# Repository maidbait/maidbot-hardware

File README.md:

# maidbot-hardware
hardware repo for the maidbot

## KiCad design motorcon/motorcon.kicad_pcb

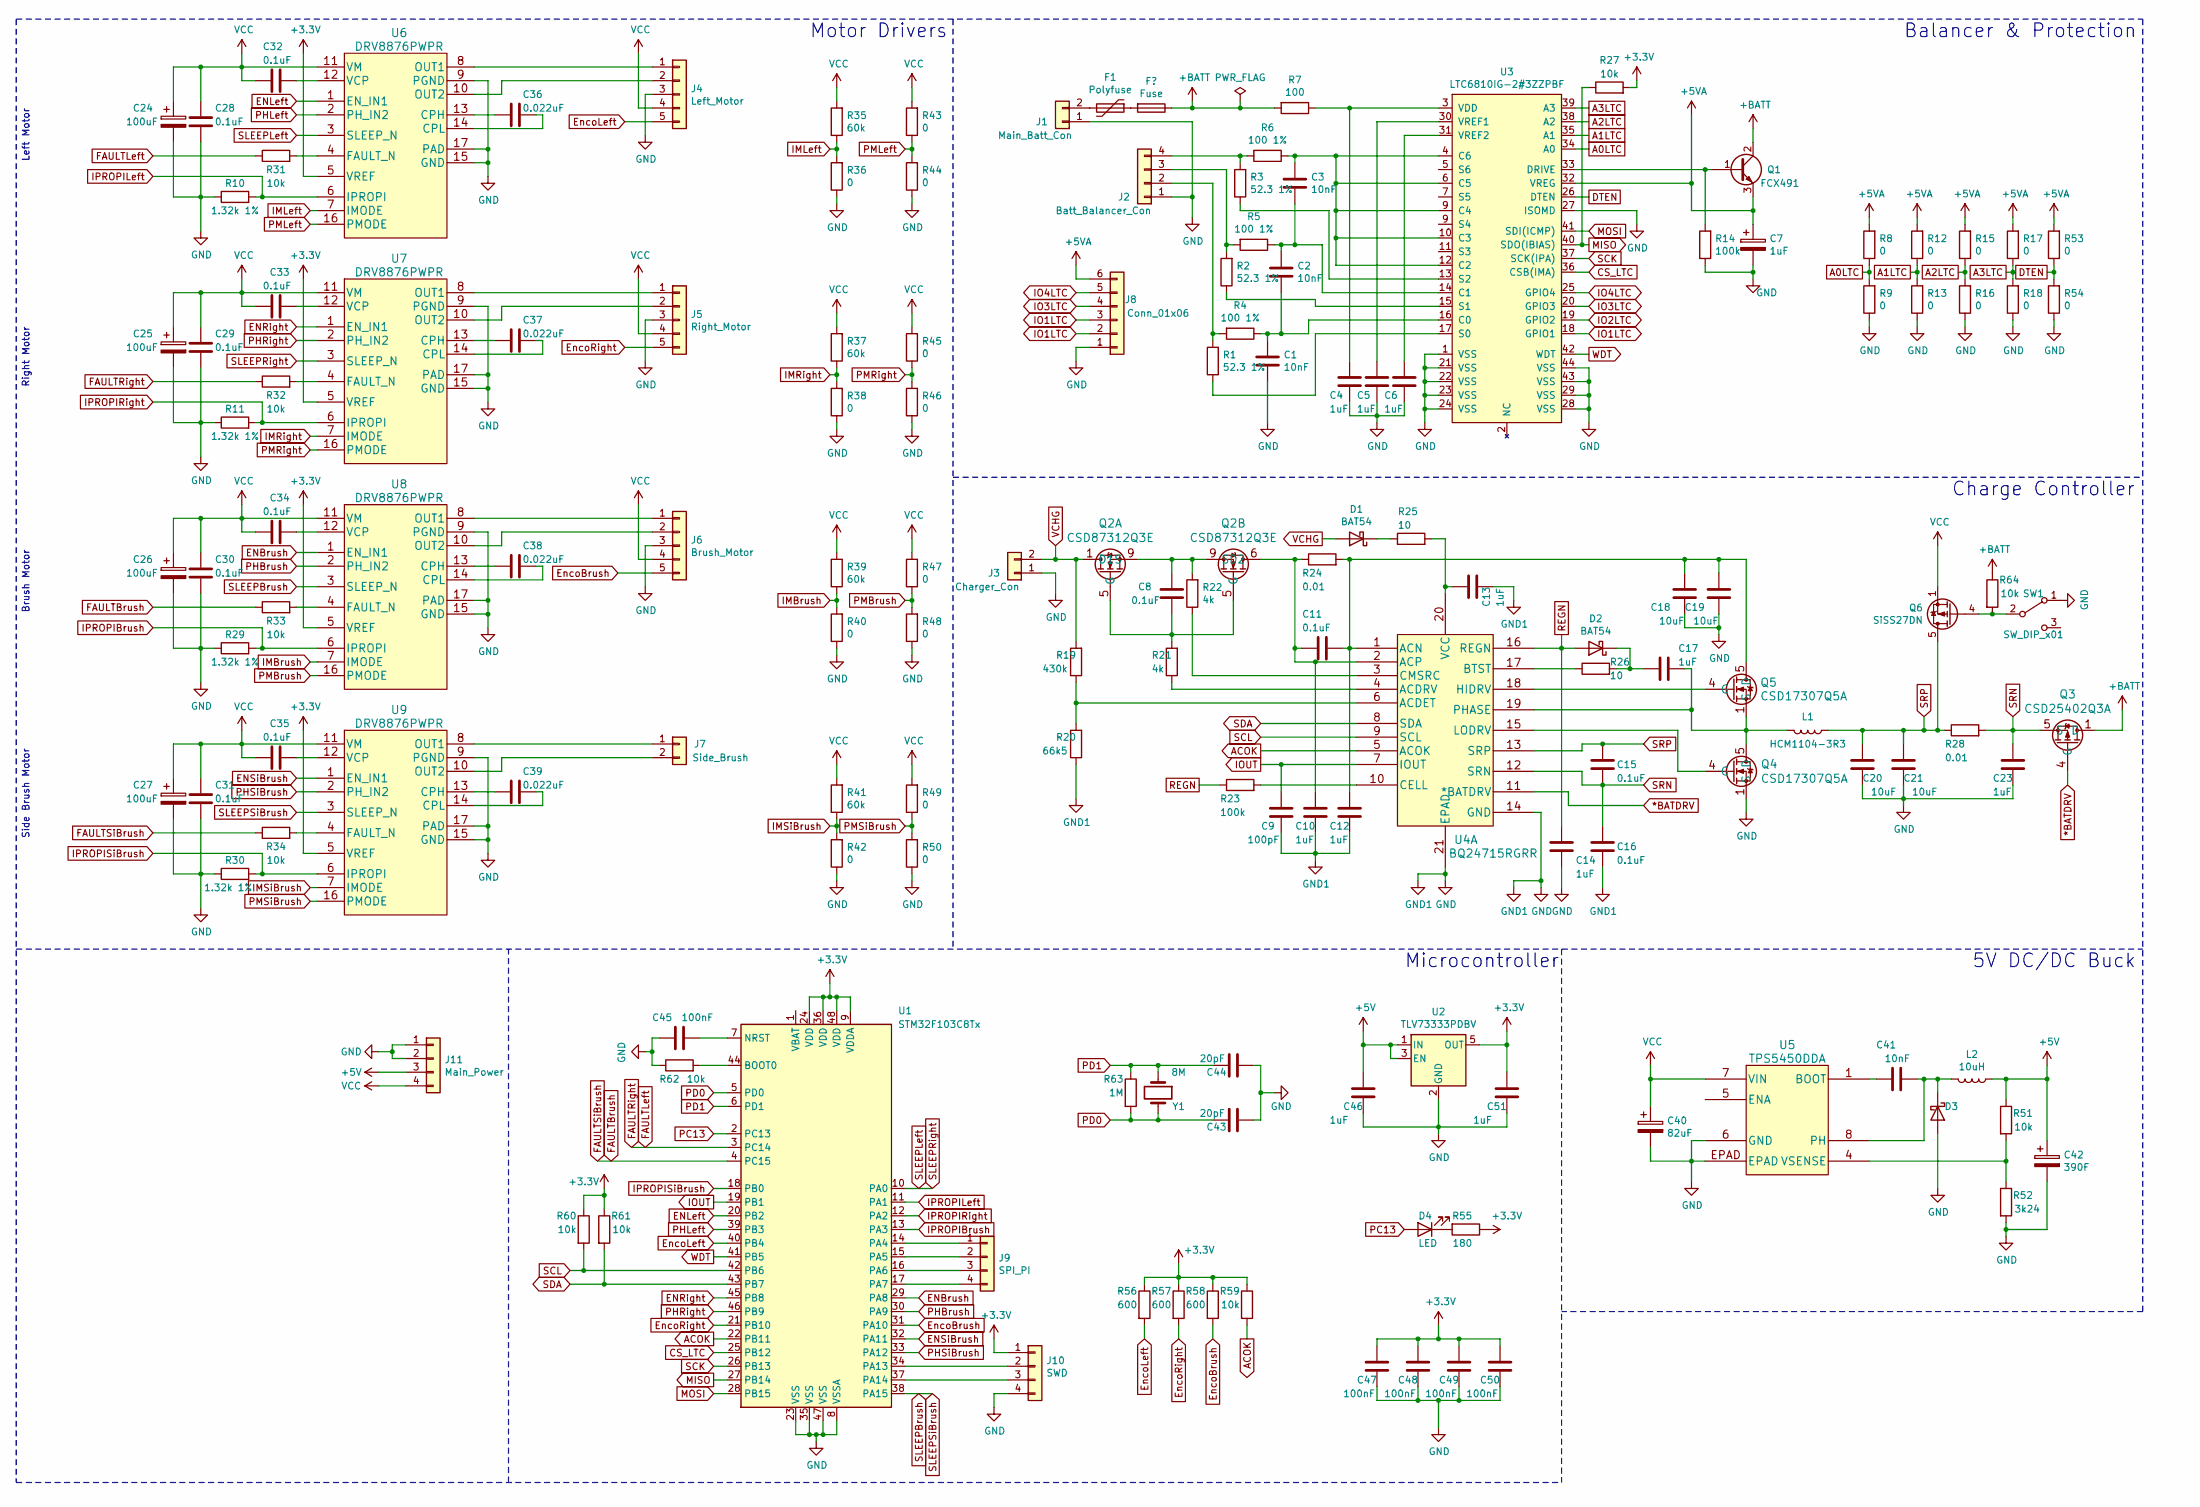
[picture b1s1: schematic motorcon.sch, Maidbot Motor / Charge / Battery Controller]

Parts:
C1, C2, C3, C41: 10nF; C_0805_2012Metric; LCSC C52278
C4, C5, C6, C10, C12, C13, C14, C17, C23, C46, C51: 1uF; C_0805_2012Metric; LCSC C282736
C7: 1uF; C_Elec_4x5.4; LCSC C3348
C8, C11, C15, C16, C28, C29, C30, C31, C32, C33, C34, C35: 0.1uF; C_0805_2012Metric; LCSC C476766
C9: 100pF; C_0805_2012Metric; LCSC C1790
C18, C19, C20, C21: 10uF; C_0805_2012Metric; LCSC C17024
C24, C25, C26, C27: 100uF; C_Radial_D6.3mm_H11.0mm_P2.50mm
C36, C37, C38, C39: 0.022uF; C_0805_2012Metric; LCSC C24658
C40: 82uF; CP_Elec_10x10; LCSC C413517
C42: 390F; CP_Elec_10x10; LCSC C359223
C43, C44: 20pF; C_0805_2012Metric; LCSC C94472
C45, C47, C48, C49, C50: 100nF; C_0805_2012Metric; LCSC C1711
D1, D2: BAT54; D_SOT-23_ANK; LCSC C369922
D3: BAT54; D_SMB; LCSC C32513
D4: LED; LED_0603_1608Metric; LCSC C84263
F1: Polyfuse; 16R1400GH
J1: Main_Batt_Con; AMASS_XT30UPB-M_1x02_P5.0mm_Vertical; LCSC C428721
J2: Batt_Balancer_Con; JST_PH_B4B-PH-K_1x04_P2.00mm_Vertical
J3: Charger_Con; JST_VH_B2P-VH_1x02_P3.96mm_Vertical; LCSC C138453
J4: Left_Motor; JST_PH_B5B-PH-K_1x05_P2.00mm_Vertical
J5: Right_Motor; JST_PH_B5B-PH-K_1x05_P2.00mm_Vertical
J6: Brush_Motor; JST_PH_B5B-PH-K_1x05_P2.00mm_Vertical
J7: Side_Brush; JST_PH_B2B-PH-K_1x02_P2.00mm_Vertical
J8: Conn_01x06; JST_PH_B5B-PH-K_1x05_P2.00mm_Vertical
J9: SPI_PI; JST_PH_B5B-PH-K_1x05_P2.00mm_Vertical
J10: SWD; JST_PH_S4B-PH-K_1x04_P2.00mm_Horizontal
J11: Main_Power; Molex_Mini-Fit_Jr_5569-04A2_2x02_P4.20mm_Horizontal; LCSC C234187
L1: HCM1104-3R3; LCSC C427317
L2: 10uH; BCIHP1770HC; LCSC C237980
Q1: FCX491; SOT-89-3; LCSC C156315
Q2: CSD87312Q3E; LCSC C553144
Q3: CSD25402Q3A; LCSC C111356
Q4, Q5: CSD17307Q5A; LCSC C139362
Q6: SiSS27DN; Vishay_PowerPAK_1212-8_Single
R1, R2, R3: 52.3 1%; R_0805_2012Metric; LCSC C334920
R4, R5, R6: 100 1%; R_0805_2012Metric; LCSC C103902
R7: 100; R_0805_2012Metric; LCSC C103909
R8, R9, R12, R13, R15, R16, R17, R18, R36, R38, R40, R42, R43, R44, R45, R46, R47, R48, R49, R50, R53, R54: 0; R_0805_2012Metric; LCSC C17477
R10, R11, R29, R30: 1.32k 1%; R_0805_2012Metric
R14, R23: 100k; R_0805_2012Metric; LCSC C149504
R19: 430k; R_0805_2012Metric; LCSC C17692
R20: 66k5; R_0805_2012Metric; LCSC C17791
R21, R22: 4k; R_0805_2012Metric; LCSC C17663
R24, R28: 0.01; R_1206_3216Metric; LCSC C309628
R25, R26: 10; R_0805_2012Metric; LCSC C17415
R27, R31, R32, R33, R34, R51, R59, R60, R61, R62, R64: 10k; R_0805_2012Metric; LCSC C17414
R35, R37, R39, R41: 60k; R_0805_2012Metric; LCSC C170940
R52: 3k24; R_0805_2012Metric; LCSC C17609
R55: 180; R_0805_2012Metric; LCSC C104048
R56, R57, R58: 600; R_0805_2012Metric; LCSC C17777
R63: 1M; R_0805_2012Metric; LCSC C17777
SW1: SW_DIP_x01; SS-12D28L4
U1: STM32F103C8Tx; LQFP-48_7x7mm_P0.5mm; LCSC C8734
U2: TLV73333PDBV; SOT-23-5; LCSC C134139
U3: LTC6810IG-2#3ZZPBF; SSOP-44
U4: BQ24715RGRR; LCSC C276341
U5: TPS5450DDA; LCSC C114425
U6, U7, U8, U9: DRV8876PWPR
Y1: 8M; Crystal_SMD_3225-4Pin_3.2x2.5mm; LCSC C400090

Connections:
*BATDRV: Q3.4 (G), U4.11 (*BATDRV)
+3V3: C47.1, C48.1, C49.1, C50.1, C51.1, J10.1, R27.2, R55.1, R56.1, R57.1, R58.1, R59.1, R60.1, R61.1, U1.9 (VDDA), U1.24 (VDD), U1.36 (VDD), U1.48 (VDD), U2.5 (OUT), U6.5 (VREF), U7.5 (VREF), U8.5 (VREF), U9.5 (VREF)
+5V: C42.1, C46.1, J11.3, L2.1, R51.1, U2.1 (IN), U2.3 (EN)
+5VA: C7.1, J8.6, Q1.3 (E), R8.2, R12.2, R15.2, R17.2, R53.2, U3.32 (VREG)
+BATT: F1.1, Q1.2 (C), Q3.1 (D), Q3.2 (D), Q3.3 (D), R7.2, R64.1
A0LTC: R8.1, R9.2, U3.34 (A0)
A1LTC: R12.1, R13.2, U3.35 (A1)
A2LTC: R15.1, R16.2, U3.38 (A2)
A3LTC: R17.1, R18.2, U3.39 (A3)
ACOK: R59.2, U1.22 (PB11), U4.5 (ACOK)
CS_LTC: U1.25 (PB12), U3.36 (CSB(IMA))
DTEN: R53.1, R54.2, U3.26 (DTEN)
ENBrush: U1.29 (PA8), U8.1 (EN_IN1)
ENLeft: U1.20 (PB2), U6.1 (EN_IN1)
ENRight: U1.45 (PB8), U7.1 (EN_IN1)
ENSiBrush: U1.32 (PA11), U9.1 (EN_IN1)
EncoBrush: J6.5, R58.2, U1.31 (PA10)
EncoLeft: J4.5, R56.2, U1.40 (PB4)
EncoRight: J5.5, R57.2, U1.21 (PB10)
FAULTBrush: R33.1, R34.1, U1.4 (PC15)
FAULTLeft: R31.1, R32.1, U1.3 (PC14)
GND: C1.2, C4.2, C5.2, C6.2, C7.2, C9.2, C10.2, C12.2, C13.2, C14.2, C16.2, C18.1, C19.1, C20.1, C21.1, C23.2, C24.2, C25.2, C26.2, C27.2, C28.2, C29.2, C30.2, C31.2, C40.2, C42.2, C43.1, C44.1, C45.1, C46.2, C47.2, C48.2, C49.2, C50.2, C51.2, D3.2 (A), J1.1, J2.1, J3.1, J4.3, J5.3, J6.3, J8.1, J10.4, J11.1, J11.2, Q4.1 (S), Q4.2 (S), Q4.3 (S), R9.1, R10.1, R11.1, R13.1, R14.1, R16.1, R18.1, R20.1, R29.1, R30.1, R36.1, R38.1, R40.1, R42.1, R44.1, R46.1, R48.1, R50.1, R52.2, R54.1, R62.1, SW1.1 (A), U1.8 (VSSA), U1.23 (VSS), U1.35 (VSS), U1.47 (VSS), U2.2 (GND), U3.1 (VSS), U3.21 (VSS), U3.22 (VSS), U3.23 (VSS), U3.24 (VSS), U3.27 (ISOMD), U3.28 (VSS), U3.29 (VSS), U3.43 (VSS), U3.44 (VSS), U4.14 (GND), U4.21 (EPAD), U5.6 (GND), U5.EPAD, U6.9 (PGND), U6.15 (GND), U6.17 (PAD), U7.9 (PGND), U7.15 (GND), U7.17 (PAD), U8.9 (PGND), U8.15 (GND), U8.17 (PAD), U9.9 (PGND), U9.15 (GND), U9.17 (PAD)
IMBrush: R39.1, R40.2, U8.7 (IMODE)
IMLeft: R35.1, R36.2, U6.7 (IMODE)
IMRight: R37.1, R38.2, U7.7 (IMODE)
IMSiBrush: R41.1, R42.2, U9.7 (IMODE)
IO1LTC: J8.2, J8.3, U3.18 (GPIO1)
IO2LTC: U3.19 (GPIO2)
IO3LTC: J8.4, U3.20 (GPIO3)
IO4LTC: J8.5, U3.25 (GPIO4)
IOUT: C9.1, U1.19 (PB1), U4.7 (IOUT)
IPROPIBrush: R29.2, U1.13 (PA3), U8.6 (IPROPI)
IPROPILeft: R10.2, U1.11 (PA1), U6.6 (IPROPI)
IPROPIRight: R11.2, U1.12 (PA2), U7.6 (IPROPI)
IPROPISiBrush: R30.2, U1.18 (PB0), U9.6 (IPROPI)
MISO: R27.1, U1.27 (PB14), U3.40 (SDO(IBIAS))
MOSI: U1.28 (PB15), U3.41 (SDI(ICMP))
unnamed: C1.1, C2.2, R4.1, U3.16 (C0)
unnamed: C2.1, C3.2, R5.1, U3.14 (C1)
unnamed: C3.1, R6.1, U3.4 (C6), U3.6 (C5), U3.9 (C4), U3.10 (C3), U3.12 (C2)
unnamed: C4.1, R7.1, U3.3 (VDD)
unnamed: C5.1, U3.30 (VREF1)
unnamed: C6.1, U3.31 (VREF2)
unnamed: C8.1, Q2.9 (S), R22.2
unnamed: C8.2, Q2.5 (G), R21.2
unnamed: C10.1, C11.2, Q2.6 (D2), Q2.7 (D2), Q2.8 (D2), R24.1, U4.2 (ACP)
unnamed: C11.1, C12.1, C18.2, C19.2, Q5.5 (D), Q5.6 (D), Q5.7 (D), Q5.8 (D), R24.2, U4.1 (ACN)
unnamed: C13.1, R25.2, U4.20 (VCC)
unnamed: C17.1, L1.2, Q4.5 (D), Q4.6 (D), Q4.7 (D), Q4.8 (D), Q5.1 (S), Q5.2 (S), Q5.3 (S), U4.19 (PHASE)
unnamed: C17.2, D2.1 (K), R26.2
unnamed: C32.1, U6.12 (VCP)
unnamed: C33.1, U7.12 (VCP)
unnamed: C34.1, U8.12 (VCP)
unnamed: C35.1, U9.12 (VCP)
unnamed: C36.1, U6.14 (CPL)
unnamed: C36.2, U6.13 (CPH)
unnamed: C37.1, U7.14 (CPL)
unnamed: C37.2, U7.13 (CPH)
unnamed: C38.1, U8.14 (CPL)
unnamed: C38.2, U8.13 (CPH)
unnamed: C39.1, U9.14 (CPL)
unnamed: C39.2, U9.13 (CPH)
unnamed: C41.1, U5.1 (BOOT)
unnamed: C41.2, D3.1 (K), L2.2, U5.8 (PH)
unnamed: C45.2, U1.7 (NRST)
unnamed: D1.1 (K), R25.1
unnamed: D4.1 (K), R55.2
unnamed: F1.2, J1.2
unnamed: J2.2, R1.2, R4.2
unnamed: J2.3, R2.2, R5.2
unnamed: J2.4, R3.2, R6.2
unnamed: J4.1, U6.8 (OUT1)
unnamed: J4.2, U6.10 (OUT2)
unnamed: J5.1, U7.8 (OUT1)
unnamed: J5.2, U7.10 (OUT2)
unnamed: J6.1, U8.8 (OUT1)
unnamed: J6.2, U8.10 (OUT2)
unnamed: J7.1, U9.8 (OUT1)
unnamed: J7.2, U9.10 (OUT2)
unnamed: J9.1, U1.14 (PA4)
unnamed: J9.2, U1.15 (PA5)
unnamed: J9.3, U1.16 (PA6)
unnamed: J9.4, U1.17 (PA7)
unnamed: J10.2, U1.34 (PA13)
unnamed: J10.3, U1.37 (PA14)
unnamed: Q1.1 (B), R14.2, U3.33 (DRIVE)
unnamed: Q4.4 (G), U4.15 (LODRV)
unnamed: Q5.4 (G), U4.18 (HIDRV)
unnamed: Q6.4 (G), R64.2, SW1.2 (B)
unnamed: R1.1, U3.17 (S0)
unnamed: R2.1, U3.15 (S1)
unnamed: R3.1, U3.13 (S2)
unnamed: R19.1, R20.2, U4.6 (ACDET)
unnamed: R21.1, U4.4 (ACDRV)
unnamed: R22.1, U4.3 (CMSRC)
unnamed: R23.2, U4.10 (CELL)
unnamed: R26.1, U4.17 (BTST)
unnamed: R31.2, U6.4 (FAULT_N)
unnamed: R32.2, U7.4 (FAULT_N)
unnamed: R33.2, U8.4 (FAULT_N)
unnamed: R34.2, U9.4 (FAULT_N)
unnamed: R51.2, R52.1, U5.4 (VSENSE)
unnamed: R62.2, U1.44 (BOOT0)
PC13: D4.2 (A), U1.2 (PC13)
PD0: C43.2, R63.2, U1.5 (PD0), Y1.2
PD1: C44.2, R63.1, U1.6 (PD1), Y1.1
PHBrush: U1.30 (PA9), U8.2 (PH_IN2)
PHLeft: U1.39 (PB3), U6.2 (PH_IN2)
PHRight: U1.46 (PB9), U7.2 (PH_IN2)
PHSiBrush: U1.33 (PA12), U9.2 (PH_IN2)
PMBrush: R47.1, R48.2, U8.16 (PMODE)
PMLeft: R43.1, R44.2, U6.16 (PMODE)
PMRight: R45.1, R46.2, U7.16 (PMODE)
PMSiBrush: R49.1, R50.2, U9.16 (PMODE)
REGN: C14.1, D2.2 (A), R23.1, U4.16 (REGN)
SCK: U1.26 (PB13), U3.37 (SCK(IPA))
SCL: R60.2, U1.42 (PB6), U4.9 (SCL)
SDA: R61.2, U1.43 (PB7), U4.8 (SDA)
SLEEPBrush: U1.38 (PA15), U8.3 (SLEEP_N), U9.3 (SLEEP_N)
SLEEPLeft: U1.10 (PA0), U6.3 (SLEEP_N), U7.3 (SLEEP_N)
SRN: C15.2, C16.1, C23.1, Q3.5 (S), Q3.6 (S), Q3.7 (S), Q3.8 (S), Q3.9 (S), R28.2, U4.12 (SRN)
SRP: C15.1, C20.2, C21.2, L1.1, Q6.5 (D), R28.1, U4.13 (SRP)
VCC: C24.1, C25.1, C26.1, C27.1, C28.1, C29.1, C30.1, C31.1, C32.2, C33.2, C34.2, C35.2, C40.1, J4.4, J5.4, J6.4, J11.4, Q6.1 (S), Q6.2 (S), Q6.3 (S), R35.2, R37.2, R39.2, R41.2, R43.2, R45.2, R47.2, R49.2, U5.7 (VIN), U6.11 (VM), U7.11 (VM), U8.11 (VM), U9.11 (VM)
VCHG: D1.2 (A), J3.2, Q2.1 (D1), Q2.2 (D1), Q2.3 (D1), Q2.4 (D1), R19.2
WDT: U1.41 (PB5), U3.42 (WDT)

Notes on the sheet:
Balancer & Protection
Charge Controller
5V DC/DC Buck
Motor Drivers
Left Motor
Right Motor
Brush Motor
Side Brush Motor
Microcontroller

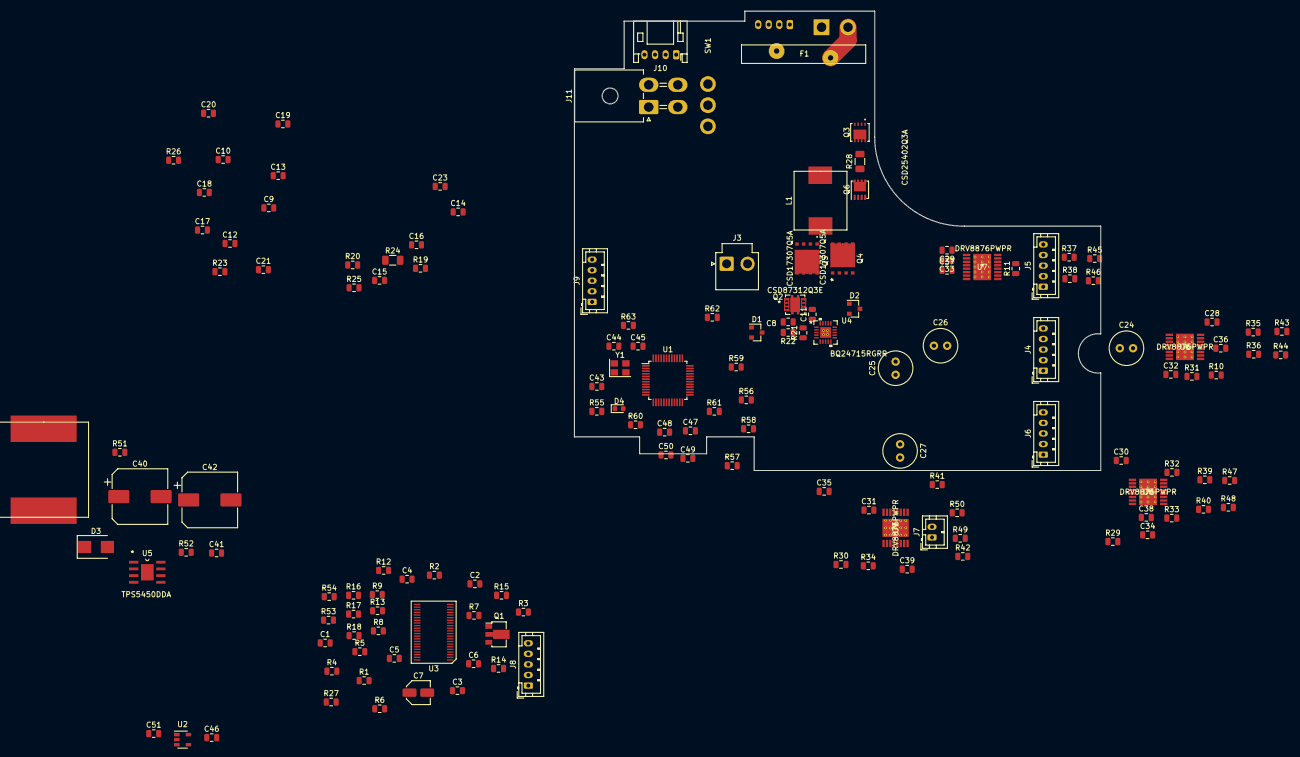
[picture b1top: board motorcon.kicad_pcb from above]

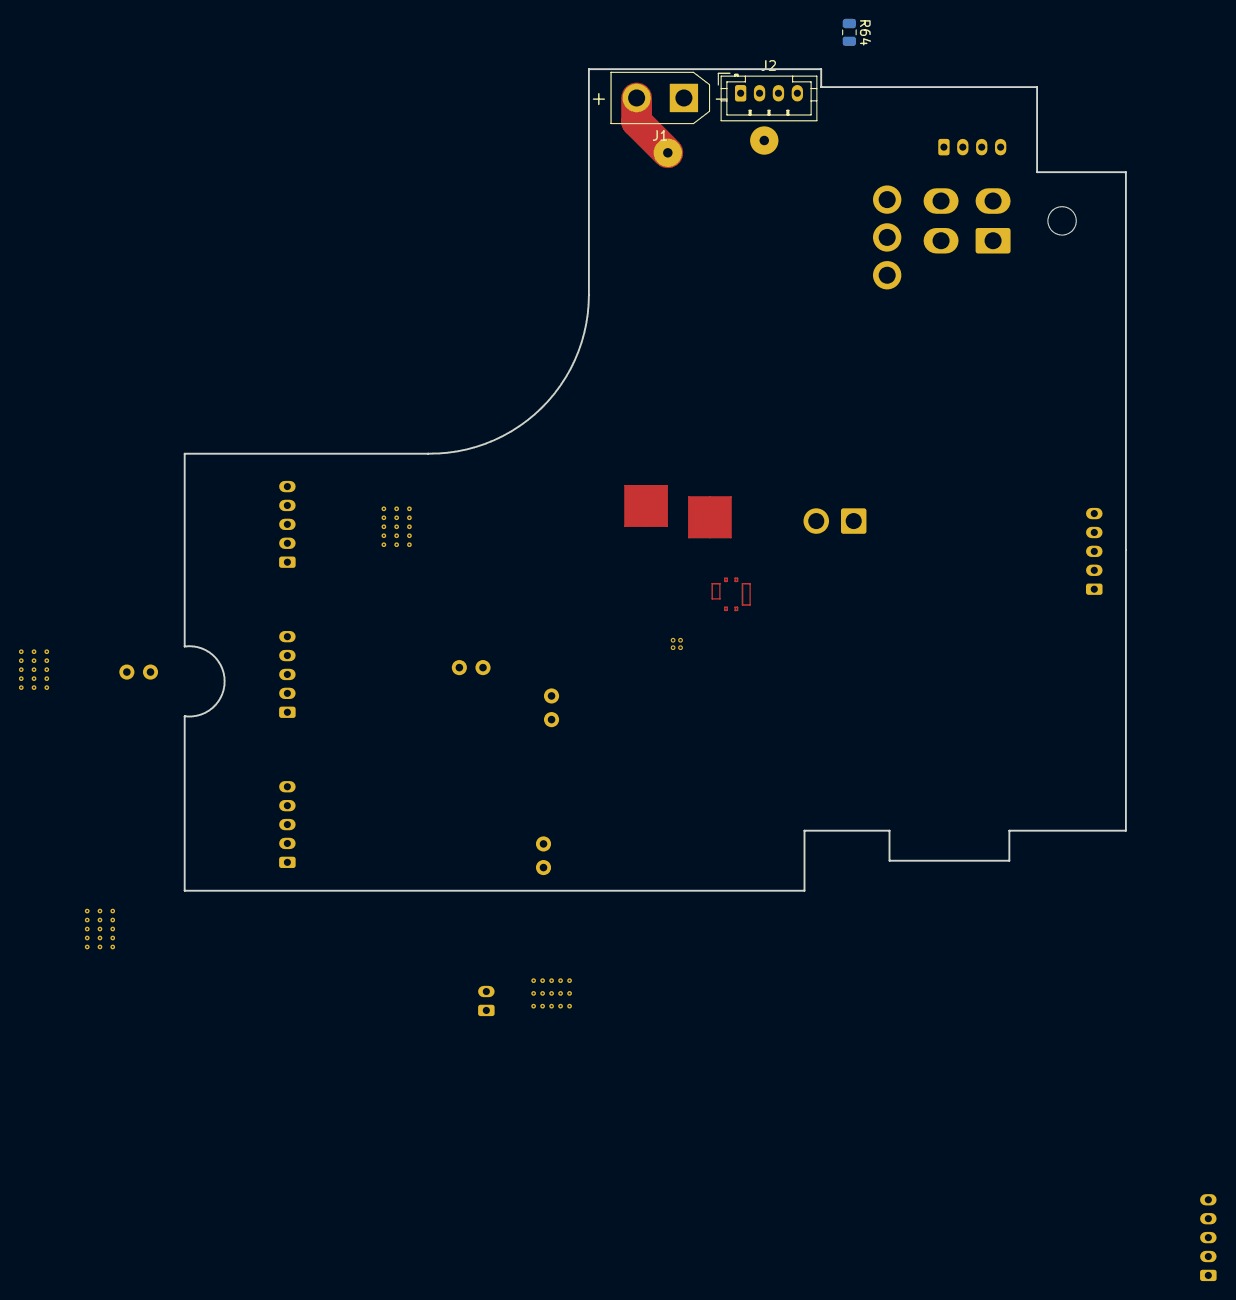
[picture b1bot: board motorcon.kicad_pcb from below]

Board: 2 copper layers, 99.6 x 86.9 mm, 149 parts (3 on the bottom side), 124 nets.

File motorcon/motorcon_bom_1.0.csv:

Component,Description,Part,References,Value,Footprint,Quantity Per PCB,Datasheet,LCSC
1,Unpolarized capacitor,C,C43 C44,20pF,C_0805_2012Metric,2,~,C94472
2,Unpolarized capacitor,C,C9,100pF,C_0805_2012Metric,1,~,C1790
3,Unpolarized capacitor,C,C1 C2 C3 C41,10nF,C_0805_2012Metric,4,~,C52278
4,Unpolarized capacitor,C,C36 C37 C38 C39,0.022uF,C_0805_2012Metric,4,~,C24658
5,Unpolarized capacitor,C,C8 C11 C15 C16 C28 C29 C30 C31 C32 C33 C34 C35 C45 C47 C48 C49 C50,0.1uF,C_0805_2012Metric,17,~,C476766 C1711
6,Unpolarized capacitor,C,C4 C5 C6 C10 C12 C13 C14 C17 C23 C46 C51,1uF,C_0805_2012Metric,11,~,C282736
7,Polarized capacitor,CP,C7,1uF,C_Elec_4x5.4,1,~,C3348
8,Unpolarized capacitor,C,C18 C19 C20 C21,10uF,C_0805_2012Metric,4,~,C17024
9,Polarized capacitor,CP,C40,82uF,CP_Elec_10x10,1,~,C413517
10,Polarized capacitor,CP,C24 C25 C26 C27,100uF,C_Radial_D6.3mm_H11.0mm_P2.50mm,4,~,
11,Polarized capacitor,CP,C42,390F,CP_Elec_10x10,1,~,C359223
12,Schottky diode,D_Schottky,D1 D2,BAT54,D_SOT-23_ANK,2,~,C369922
13,Schottky diode,D_Schottky,D3,BAT54,D_SMB,1,~,C32513
14,Light emitting diode,LED,D4,LED,LED_0603_1608Metric,1,~,C84263
15,"Generic connector, single row, 01x04, script generated (kicad-library-utils/schlib/autogen/connector/)",Conn_01x04,J2,Batt_Balancer_Con,JST_PH_S4B-PH-K_1x04_P2.00mm_Horizontal,1,~,
16,"Generic connector, single row, 01x02, script generated (kicad-library-utils/schlib/autogen/connector/)",Conn_01x02,J3,Charger_Con,JST_VH_B2P-VH_1x02_P3.96mm_Vertical,1,~,C138453
17,"Generic connector, single row, 01x06, script generated (kicad-library-utils/schlib/autogen/connector/)",Conn_01x06,J8,Conn_01x06,JST_PH_S6B-PH-SM4-TB_1x06-1MP_P2.00mm_Horizontal,1,~,
18,"Generic connector, single row, 01x05, script generated (kicad-library-utils/schlib/autogen/connector/)",Conn_01x05,J4 J5 J6,Left_Motor,JST_PH_S5B-PH-SM4-TB_1x05-1MP_P2.00mm_Horizontal,3,~,
19,"Generic connector, single row, 01x02, script generated (kicad-library-utils/schlib/autogen/connector/)",Conn_01x02,J1,Main_Batt_Con,AMASS_XT30PW-M_1x02_P2.50mm_Horizontal,1,~,C431092
20,"Generic connector, single row, 01x04, script generated (kicad-library-utils/schlib/autogen/connector/)",Conn_01x04,J11,Main_Power,Molex_Mini-Fit_Jr_5569-04A2_2x02_P4.20mm_Horizontal,1,~,C234187
21,"Generic connector, single row, 01x04, script generated (kicad-library-utils/schlib/autogen/connector/)",Conn_01x04,J9,SPI_PI,JST_PH_S4B-PH-SM4-TB_1x04-1MP_P2.00mm_Horizontal,1,~,
22,"Generic connector, single row, 01x03, script generated (kicad-library-utils/schlib/autogen/connector/)",Conn_01x03,J10,SWD,PinHeader_1x03_P2.54mm_Horizontal,1,~,
23,"Generic connector, single row, 01x02, script generated (kicad-library-utils/schlib/autogen/connector/)",Conn_01x02,J7,Side_Brush,JST_PH_S2B-PH-SM4-TB_1x02-1MP_P2.00mm_Horizontal,1,~,
24,Inductor,L,L2,10uH,BCIHP1770HC,1,~,C237980
25,Inductor,L,L1,HCM1104-3R3,HCM1104-3R3,1,~,C427317
26,,CSD17307Q5A-CSD17307Q5A,Q4 Q5,CSD17307Q5A,CSD17307Q5A,2,,C139362
27,,CSD25402Q3A-CSD25402Q3A,Q3,CSD25402Q3A,CSD25402Q3A,1,,C111356
28,,CSD87312Q3E-CSD87312Q3E,Q2,CSD87312Q3E,CSD87312Q3E,1,,C553144
29,"NPN transistor, base/collector/emitter",Q_NPN_BCE,Q1,FCX491,SOT-89-3,1,~,C156315
30,Resistor,R,R8 R9 R12 R13 R15 R16 R17 R18 R36 R38 R40 R42 R43 R44 R45 R46 R47 R48 R49 R50 R53 R54,0,R_0805_2012Metric,22,~,C17477
31,Resistor,R,R24 R28,0.01,R_1206_3216Metric,2,~,C309628
32,Resistor,R,R25 R26,10,R_0805_2012Metric,2,~,C17415
33,Resistor,R,R7,100,R_0805_2012Metric,1,~,C103909
34,Resistor,R,R55,180,R_0805_2012Metric,1,~,C104048
35,Resistor,R,R56 R57 R58,600,R_0805_2012Metric,3,~,C17777
36,Resistor,R,R52,3k24,R_0805_2012Metric,1,~,C17609
37,Resistor,R,R21 R22,4k,R_0805_2012Metric,2,~,C17663
38,Resistor,R,R27 R31 R32 R33 R34 R51 R59 R60 R61 R62,10k,R_0805_2012Metric,10,~,C17414
39,Resistor,R,R35 R37 R39 R41,60k,R_0805_2012Metric,4,~,C170940
40,Resistor,R,R20,66k5,R_0805_2012Metric,1,~,C17791
41,Resistor,R,R14 R23,100k,R_0805_2012Metric,2,~,C149504
42,Resistor,R,R19,430k,R_0805_2012Metric,1,~,C17692
43,Resistor,R,R10 R11 R29 R30,1.32k 1%,R_0805_2012Metric,4,~,
44,Resistor,R,R4 R5 R6,100 1%,R_0805_2012Metric,3,~,C103902
45,Resistor,R,R1 R2 R3,52.3 1%,R_0805_2012Metric,3,~,C334920
46,,BQ24715RGRR-BQ24715RGRR,U4,BQ24715RGRR,BQ24715RGRR,1,,C276341
47,,DRV8876PWPR-DRV8876PWPR,U6 U7 U8 U9,DRV8876PWPR,DRV8876PWPR,4,,
48,,LTC6810IG-2#3ZZPBF-LTC6810-2,U3,LTC6810IG-2#3ZZPBF,SSOP-44,1,https://www.analog.com/media/en/technical-documentation/data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,
49,"ARM Cortex-M3 MCU, 64KB flash, 20KB RAM, 72MHz, 2-3.6V, 37 GPIO, LQFP-48",STM32F103C8Tx,U1,STM32F103C8Tx,LQFP-48_7x7mm_P0.5mm,1,http://www.st.com/st-web-ui/static/active/en/resource/techni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,C8734
50,"300mA Capacitor-Free Low Dropout Voltage Regulator, Fixed Output 3.3V, SOT-23-5",TLV73333PDBV,U2,TLV73333PDBV,SOT-23-5,1,http://www.ti.com/lit/ds/symlink/tlv733p.pdf,C134139
51,,TPS5450DDA-TPS5450DDA,U5,TPS5450DDA,TPS5450DDA,1,,C114425
52,Two pin crystal,Crystal,Y1,8M,Crystal_SMD_3225-4Pin_3.2x2.5mm,1,~,C400090





Component Groups:,52
Component Count:,144
Fitted Components:,144
Number of PCBs:,1
Total components:,144
Schematic Version:,1.0
Schematic Date:,2020-07-27
PCB Variant:,['default']
BoM Date:,Tue 28 Jul 2020 03:21:28 AM CEST
Schematic Source:,motorcon.sch
KiCad Version:,Eeschema 5.1.6

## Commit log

2020-07-23 Create LICENSE
2020-07-23 Adding files
2020-07-25 Progress
2020-07-27 Finished Schematic, added custom footprints
2020-07-28 did the BOM
2020-07-28 started pcb work
2020-07-29 Added layout of the pcb
2020-07-29 PCB Stuff
2020-07-30 stuff
2020-07-31 stuffs
2020-07-31 Added switch and mosfet
2020-07-31 started organizing layout
2020-08-06 working on the layout, fixes on the schematic
2020-08-06 more layout stuff

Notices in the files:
parts and their libraries:
Copyright 2016 Accelerated Designs. All rights reserved.
